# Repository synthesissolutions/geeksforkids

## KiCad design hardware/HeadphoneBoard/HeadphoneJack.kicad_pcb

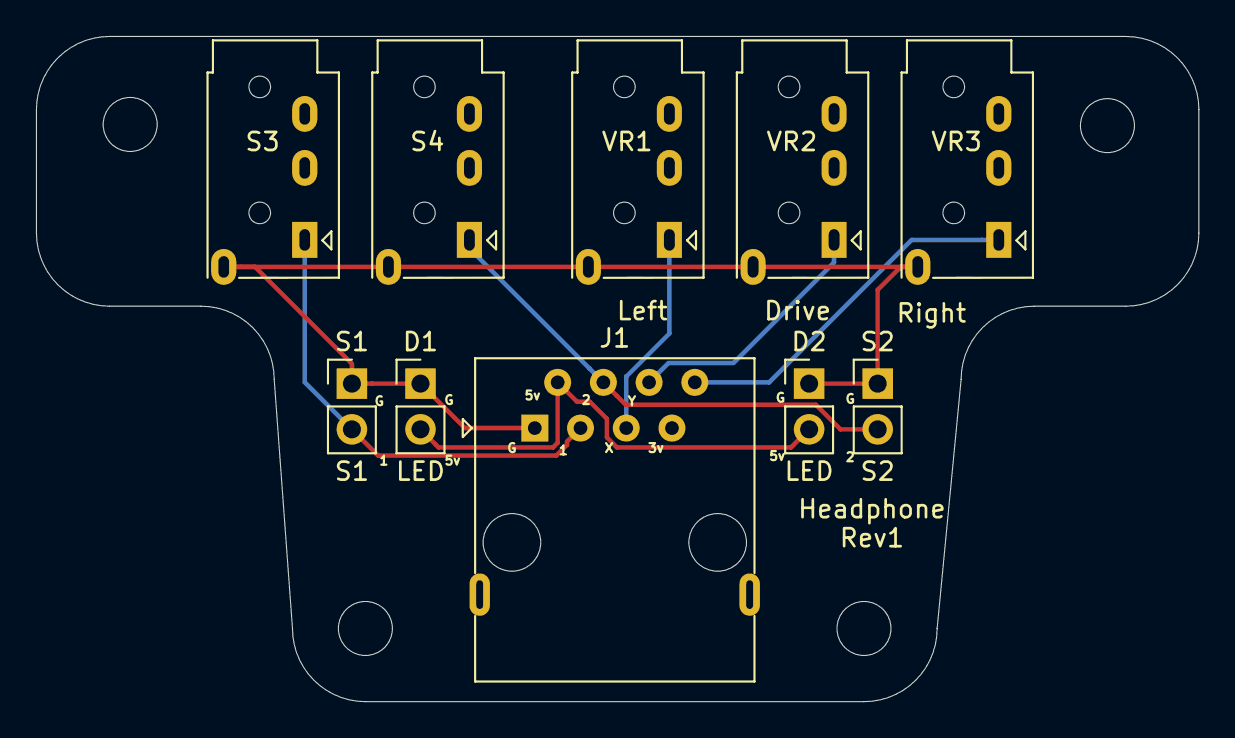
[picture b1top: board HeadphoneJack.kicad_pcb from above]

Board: 2 copper layers, 64.6 x 37.0 mm, 10 parts (0 on the bottom side), 7 nets.

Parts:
D1, D2: LED; PinHeader_1x02_P2.54mm_Vertical
J1: 8P8C; RJ45_x08_Horizontal_tabs
S1: S1; PinHeader_1x02_P2.54mm_Vertical
S2: S2; PinHeader_1x02_P2.54mm_Vertical
S3: S1; Jack_3.5mm_PJ320A_Horizontal_Short
S4: S2; Jack_3.5mm_PJ320A_Horizontal_Short
VR1: Left; Jack_3.5mm_PJ320A_Horizontal_Short
VR2: Drive; Jack_3.5mm_PJ320A_Horizontal_Short
VR3: Right; Jack_3.5mm_PJ320A_Horizontal_Short

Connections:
+5V: D1.2, D2.2, J1.2
GND: D1.1, D2.1, J1.1, S1.1, S2.1, S3.S, S4.S, VR1.S, VR2.S, VR3.S
unnamed: J1.3, S1.2, S3.T
unnamed: J1.4, S2.2, S4.T
unnamed: J1.5, VR1.T
unnamed: J1.6, VR2.T
unnamed: J1.8, VR3.T

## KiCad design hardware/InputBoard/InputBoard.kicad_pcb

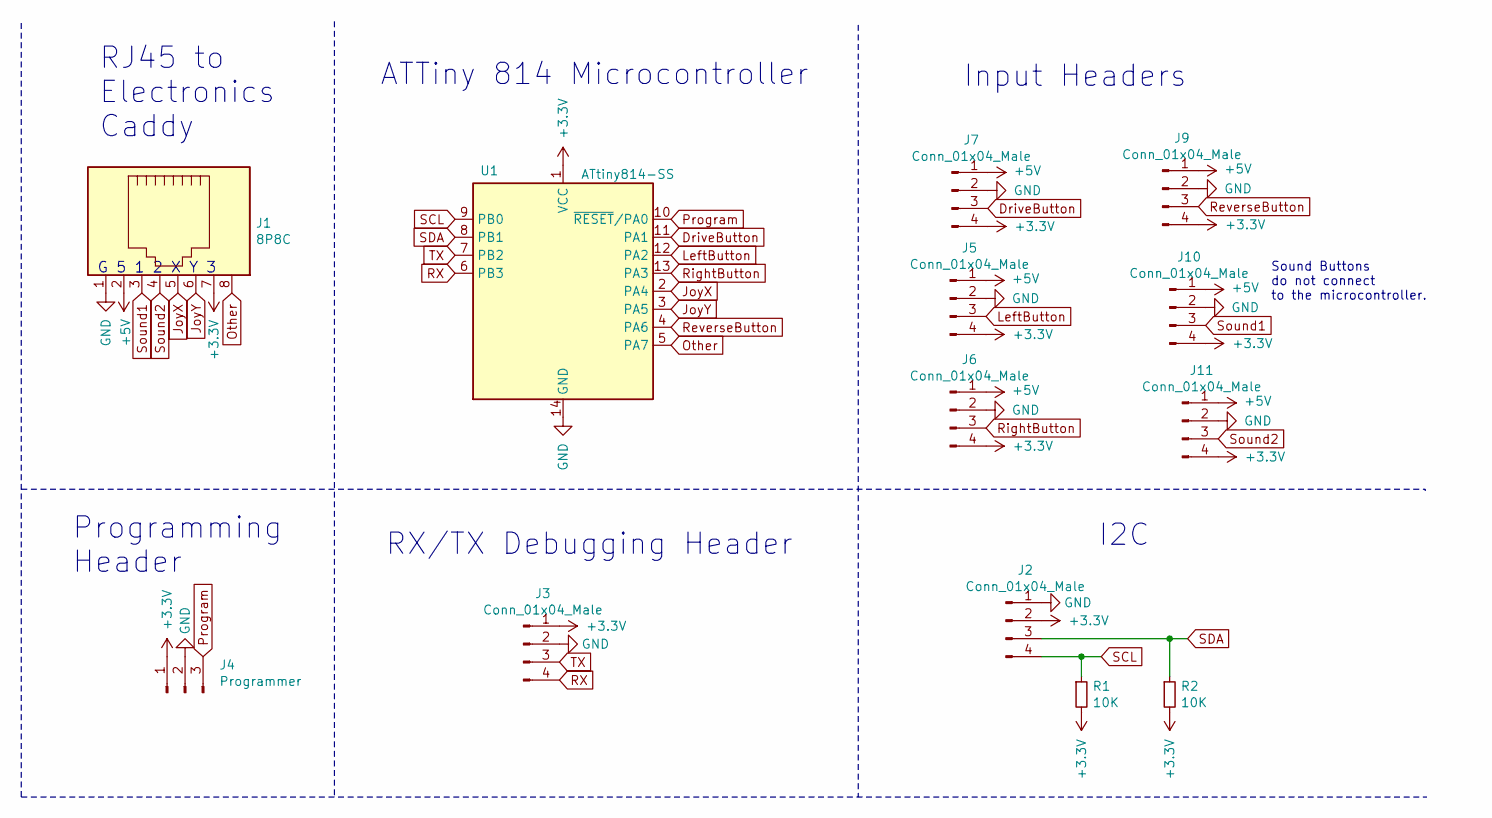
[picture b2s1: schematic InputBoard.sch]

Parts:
J1: 8P8C; RJ45_x08_Horizontal_tabs
J2: Conn_01x04_Male; JST_SH_SM04B-SRSS-TB_1x04-1MP_P1.00mm_Horizontal
J3, J5, J6, J7, J9, J10, J11: Conn_01x04_Male; PinHeader_1x04_P2.54mm_Vertical
J4: Programmer; PinHeader_1x03_P2.54mm_Vertical
R1, R2: 10K; R_0805_2012Metric_Pad1.15x1.40mm_HandSolder
U1: ATtiny814-SS; SOIC-14_3.9x8.7mm_P1.27mm

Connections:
+3V3: J1.7, J2.2, J3.1, J4.1, J5.4, J6.4, J7.4, J9.4, J10.4, J11.4, R1.2, R2.2, U1.1 (VCC)
+5V: J1.2, J5.1, J6.1, J7.1, J9.1, J10.1, J11.1
DriveButton: J7.3, U1.11 (PA1)
GND: J1.1, J2.1, J3.2, J4.2, J5.2, J6.2, J7.2, J9.2, J10.2, J11.2, U1.14 (GND)
JoyX: J1.5, U1.2 (PA4)
JoyY: J1.6, U1.3 (PA5)
LeftButton: J5.3, U1.12 (PA2)
Other: J1.8, U1.5 (PA7)
Program: J4.3, U1.10 (~RESET~/PA0)
RX: J3.4, U1.6 (PB3)
ReverseButton: J9.3, U1.4 (PA6)
RightButton: J6.3, U1.13 (PA3)
SCL: J2.4, R1.1, U1.9 (PB0)
SDA: J2.3, R2.1, U1.8 (PB1)
Sound1: J1.3, J10.3
Sound2: J1.4, J11.3
TX: J3.3, U1.7 (PB2)

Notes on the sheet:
G 5 1 2 X Y 3
Input Headers
Sound Buttons do not connect to the microcontroller.
ATTiny 814 Microcontroller
RJ45 to Electronics Caddy
Programming Header
RX/TX Debugging Header
I2C

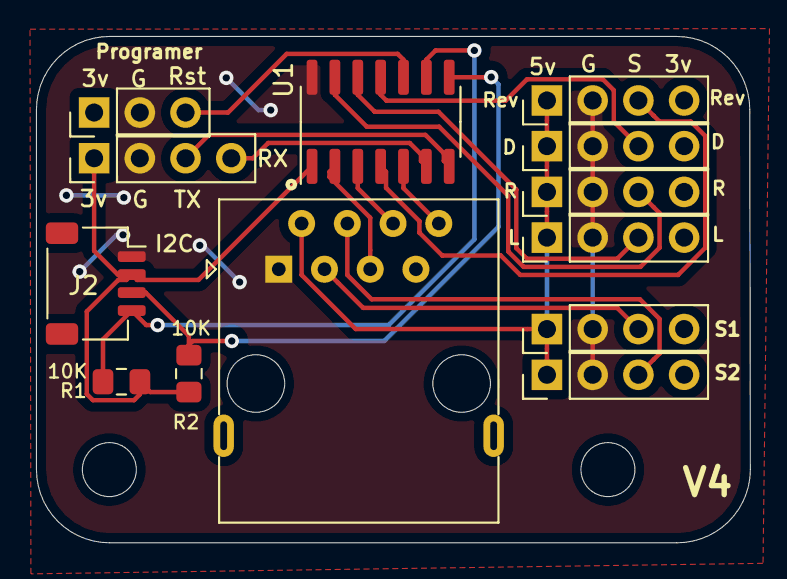
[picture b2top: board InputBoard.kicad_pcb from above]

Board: 2 copper layers, 39.7 x 28.1 mm, 13 parts (0 on the bottom side), 17 nets.

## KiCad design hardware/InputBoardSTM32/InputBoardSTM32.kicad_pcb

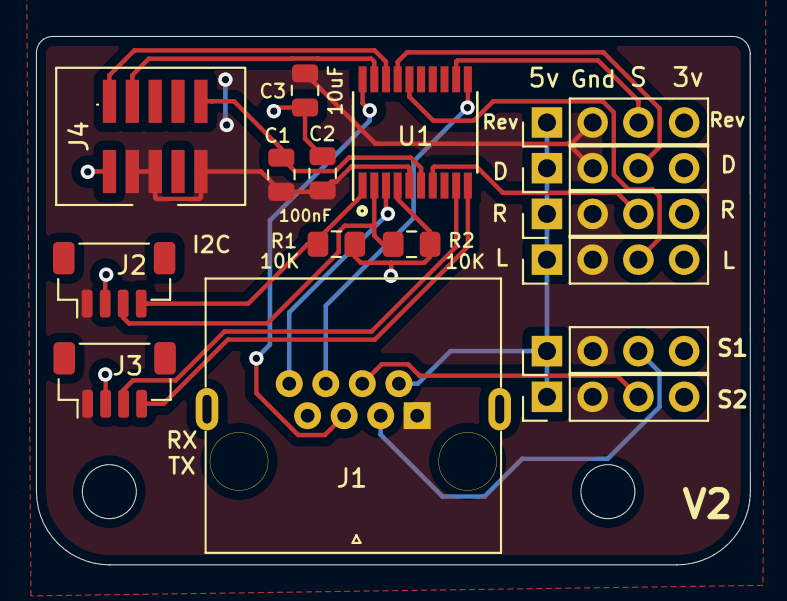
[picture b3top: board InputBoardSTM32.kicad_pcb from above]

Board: 2 copper layers, 39.7 x 29.4 mm, 16 parts (0 on the bottom side), 19 nets.

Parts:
C1, C2: 100nF; C_0805_2012Metric
C3: 10uF; C_0805_2012Metric
J1: 8P8C; RJ45_x08_Tab_Up
J2, J3: Conn_01x04_Male; JST_SH_BM04B-SRSS-TB_1x04-1MP_P1.00mm_Vertical
J4: Conn_ARM_JTAG_SWD_10; JTAG_SWD_SMD
J5, J6, J7, J9, J10, J11: Conn_01x04_Male; PinHeader_1x04_P2.54mm_Vertical
R1, R2: 10K; R_0805_2012Metric_Pad1.15x1.40mm_HandSolder
U1: STM32G031F4Px; TSSOP-20_4.4x6.5mm_P0.65mm

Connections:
+3V3: C2.1, C3.1, J1.7, J2.2, J3.2, J4.1, J5.4, J6.4, J7.4, J9.4, J10.4, J11.4, R1.2, R2.2, U1.4
+5V: J1.2, J5.1, J6.1, J7.1, J9.1, J10.1, J11.1
/RESET: C1.1, J4.10, U1.6
DriveButton: J7.3, U1.17
GND: C1.2, C2.2, C3.2, J1.1, J2.1, J3.1, J4.3, J4.5, J4.9, J5.2, J6.2, J7.2, J9.2, J10.2, J11.2, U1.5
JoyX: J1.5, U1.20
JoyY: J1.6, U1.11
LeftButton: J5.3, U1.16
Other: J1.8, U1.3
RX: J3.4, U1.10
ReverseButton: J9.3, U1.12
RightButton: J6.3, U1.7
SCL: J2.4, R1.1, U1.1
SDA: J2.3, R2.1, U1.2
SWCLK: J4.4, U1.19
SWDIO: J4.2, U1.18
Sound1: J1.3, J10.3
Sound2: J1.4, J11.3
TX: J3.3, U1.9

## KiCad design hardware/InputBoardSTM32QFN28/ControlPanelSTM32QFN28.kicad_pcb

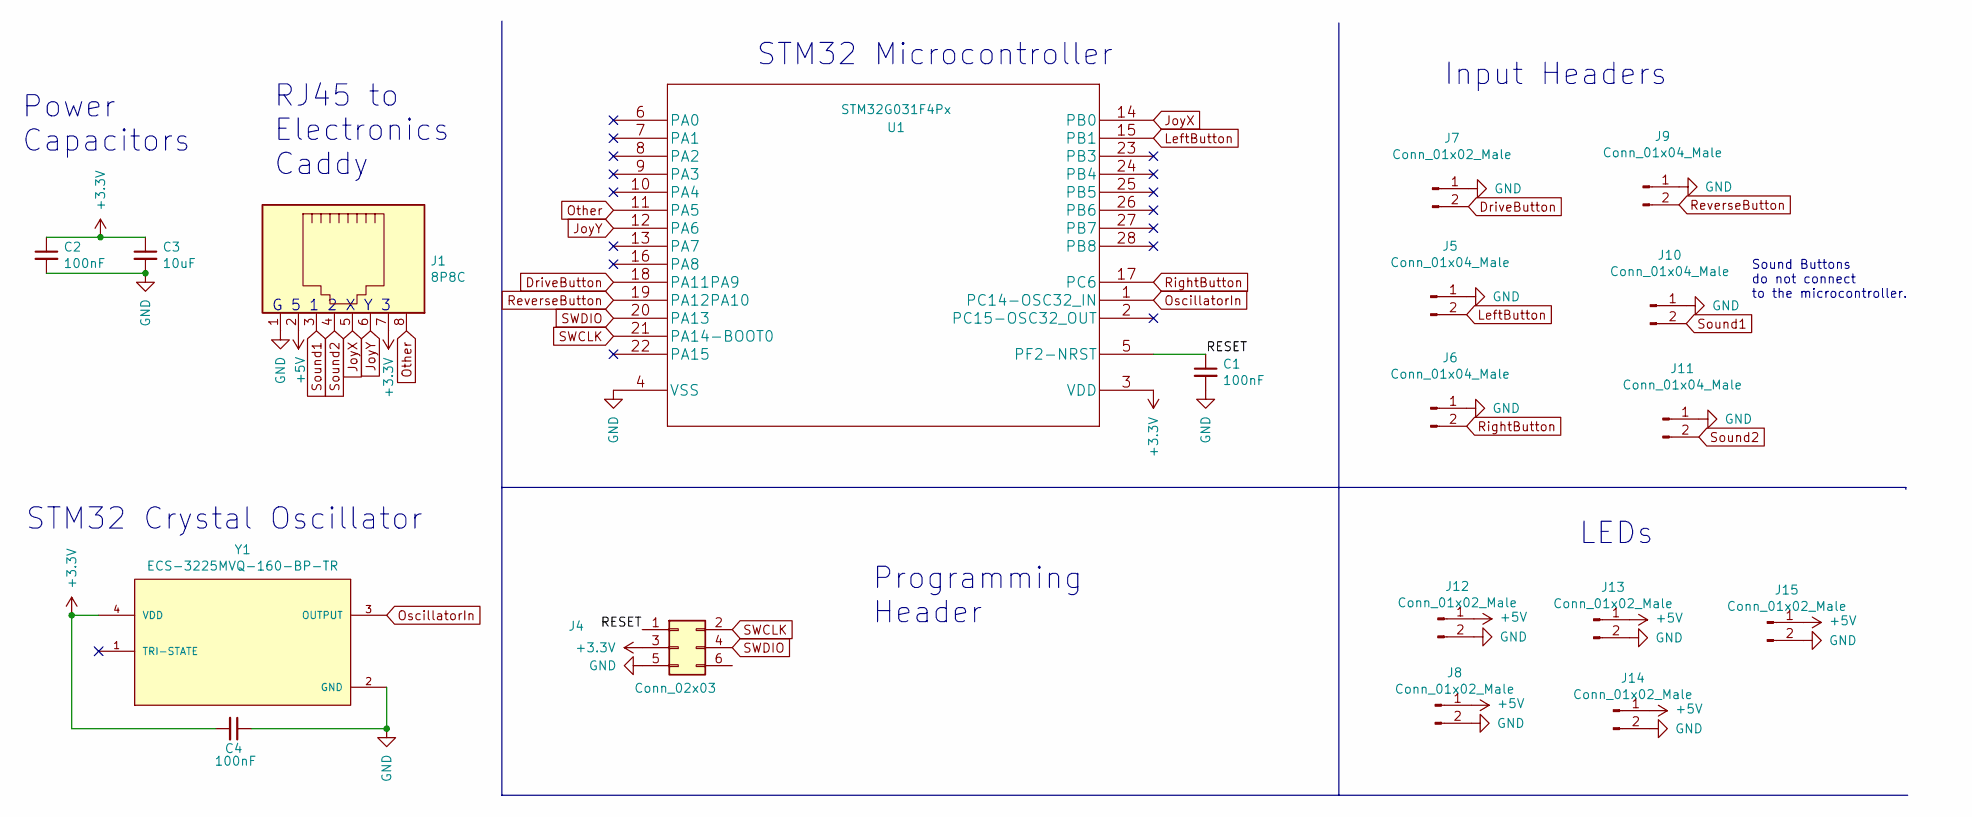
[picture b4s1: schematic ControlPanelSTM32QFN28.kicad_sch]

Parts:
C1, C2, C4: 100nF; C_0805_2012Metric
C3: 10uF; C_0805_2012Metric
J1: 8P8C; RJ45_x08_Tab_Up
J4: Conn_02x03; PinHeader_2x03_P2.54mm_Vertical
J5, J6, J9, J10, J11: Conn_01x04_Male; JST_XH_B2B-XH-A_1x02_P2.50mm_Vertical
J7, J8, J12, J13, J14, J15: Conn_01x02_Male; JST_XH_B2B-XH-A_1x02_P2.50mm_Vertical
U1: STM32G031F4Px; STM32G031G8U6
Y1: ECS-3225MVQ-160-BP-TR; OSC_ECS-3225MVQ-160-BP-TR

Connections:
+3V3: C2.1, C3.1, C4.2, J1.7, J4.3, U1.3 (VDD), Y1.4 (VDD)
+5V: J1.2, J8.1, J12.1, J13.1, J14.1, J15.1
/RESET: C1.1, J4.1, U1.5 (PF2-NRST)
DriveButton: J7.2, U1.18 (PA11PA9)
GND: C1.2, C2.2, C3.2, C4.1, J1.1, J4.5, J5.1, J6.1, J7.1, J8.2, J9.1, J10.1, J11.1, J12.2, J13.2, J14.2, J15.2, U1.4 (VSS), Y1.2 (GND)
JoyX: J1.5, U1.14 (PB0)
JoyY: J1.6, U1.12 (PA6)
LeftButton: J5.2, U1.15 (PB1)
OscillatorIn: U1.1 (PC14-OSC32_IN), Y1.3 (OUTPUT)
Other: J1.8, U1.11 (PA5)
ReverseButton: J9.2, U1.19 (PA12PA10)
RightButton: J6.2, U1.17 (PC6)
SWCLK: J4.2, U1.21 (PA14-BOOT0)
SWDIO: J4.4, U1.20 (PA13)
Sound1: J1.3, J10.2
Sound2: J1.4, J11.2

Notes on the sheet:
STM32 Microcontroller
RJ45 to Electronics Caddy
LEDs
Programming Header
Power Capacitors
Input Headers
STM32 Crystal Oscillator
G 5 1 2 X Y 3
Sound Buttons do not connect to the microcontroller.

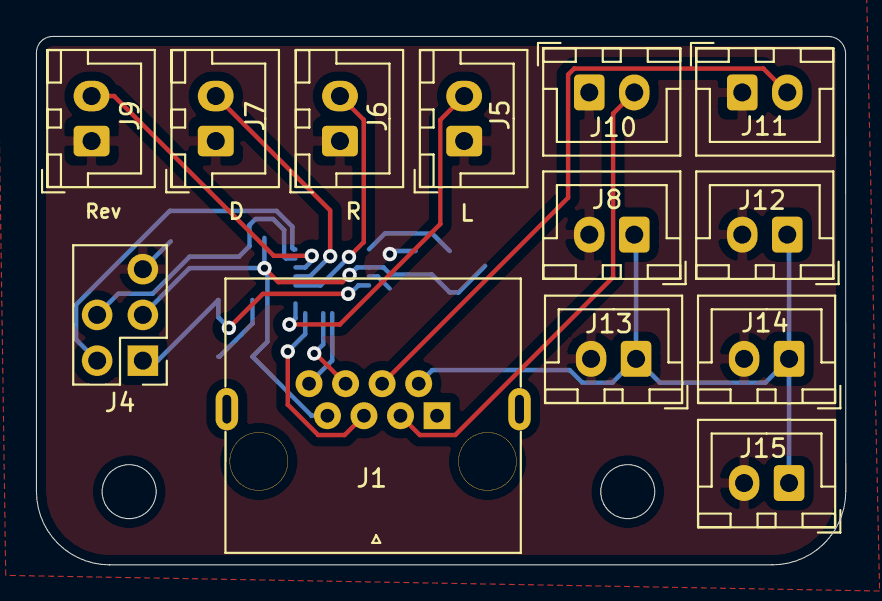
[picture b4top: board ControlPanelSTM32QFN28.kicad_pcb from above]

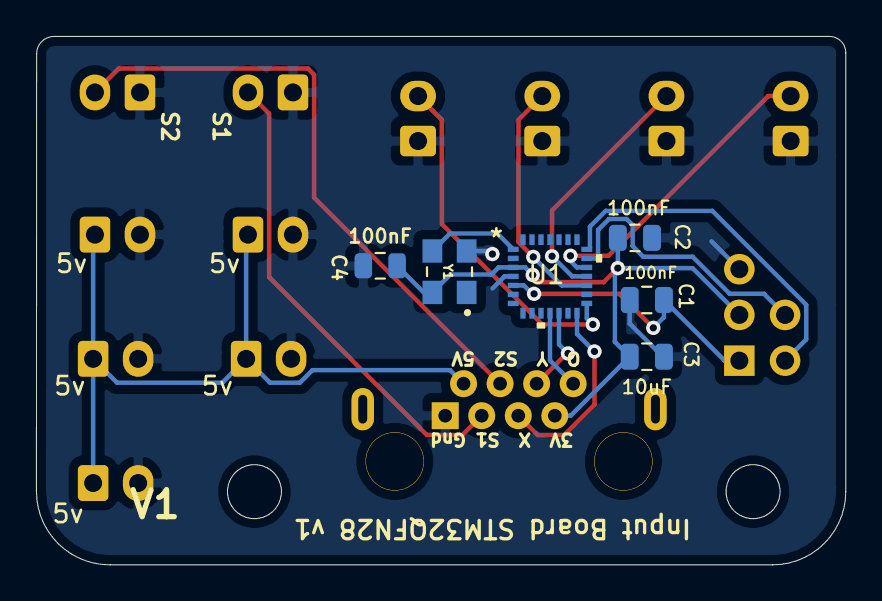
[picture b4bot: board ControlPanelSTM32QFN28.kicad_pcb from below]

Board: 2 copper layers, 45.0 x 29.4 mm, 19 parts (6 on the bottom side), 16 nets.

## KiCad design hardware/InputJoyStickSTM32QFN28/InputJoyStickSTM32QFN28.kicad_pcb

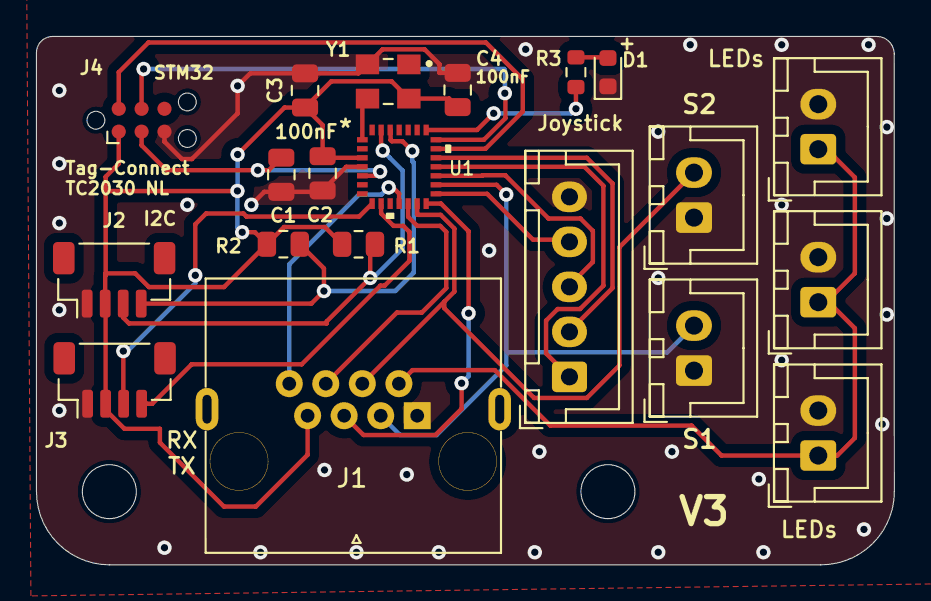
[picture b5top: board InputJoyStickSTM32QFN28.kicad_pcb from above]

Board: 2 copper layers, 47.7 x 29.4 mm, 20 parts (0 on the bottom side), 22 nets.

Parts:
C1, C2, C4: 100nF; C_0805_2012Metric
C3: 10uF; C_0805_2012Metric
D1: LED_Small; LED_0603_1608Metric
J1: 8P8C; RJ45_x08_Tab_Up
J2, J3: Conn_01x04_Male; JST_SH_BM04B-SRSS-TB_1x04-1MP_P1.00mm_Vertical
J4: TagConnect_TC2030-NL; Tag-Connect_TC2030-IDC-NL_2x03_P1.27mm_Vertical
J5: Conn_01x05_Male; JST_XH_B5B-XH-A_1x05_P2.50mm_Vertical
J6, J7, J8, J9, J10: Conn_01x02_Male; JST_XH_B2B-XH-A_1x02_P2.50mm_Vertical
R1, R2: 10K; R_0805_2012Metric
R3: 470; R_0603_1608Metric
U1: STM32G031F4Px; STM32G031G8U6
Y1: ECS-3225MVQ-160-BP-TR; OSC_ECS-3225MVQ-160-BP-TR

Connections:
+3V3: C2.1, C3.1, C4.2, J1.7, J2.2, J3.2, J4.1 (VCC), R1.2, R2.2, U1.3 (VDD), Y1.4 (VDD)
+5V: J1.2, J7.1, J9.1, J10.1
/RESET: C1.1, J4.3 (~RESET), U1.5 (PF2-NRST)
DriveButton: J5.1, U1.18 (PA11PA9)
GND: C1.2, C2.2, C3.2, C4.1, D1.1 (K), J1.1, J2.1, J3.1, J4.5 (GND), J5.5, J6.1, J7.2, J8.1, J9.2, J10.2, U1.4 (VSS), Y1.2 (GND)
JoyX: J1.5, U1.14 (PB0)
JoyY: J1.6, U1.12 (PA6)
LeftButton: J5.4, U1.15 (PB1)
unnamed: D1.2 (A), R3.1
OscillatorIn: U1.1 (PC14-OSC32_IN), Y1.3 (OUTPUT)
Other: J1.8, U1.11 (PA5)
RX: J3.4, U1.9 (PA3)
ReverseButton: J5.2, U1.19 (PA12PA10)
RightButton: J5.3, U1.17 (PC6)
SCL: J2.4, R1.1, U1.26 (PB6)
SDA: J2.3, R2.1, U1.27 (PB7)
SWCLK: J4.4 (SWCLK), U1.21 (PA14-BOOT0)
SWDIO: J4.2 (SWDIO), U1.20 (PA13)
Sound1: J1.3, J6.2, U1.16 (PA8)
Sound2: J1.4, J8.2, U1.13 (PA7)
TX: J3.3, U1.8 (PA2)
USER_LED: R3.2, U1.22 (PA15)

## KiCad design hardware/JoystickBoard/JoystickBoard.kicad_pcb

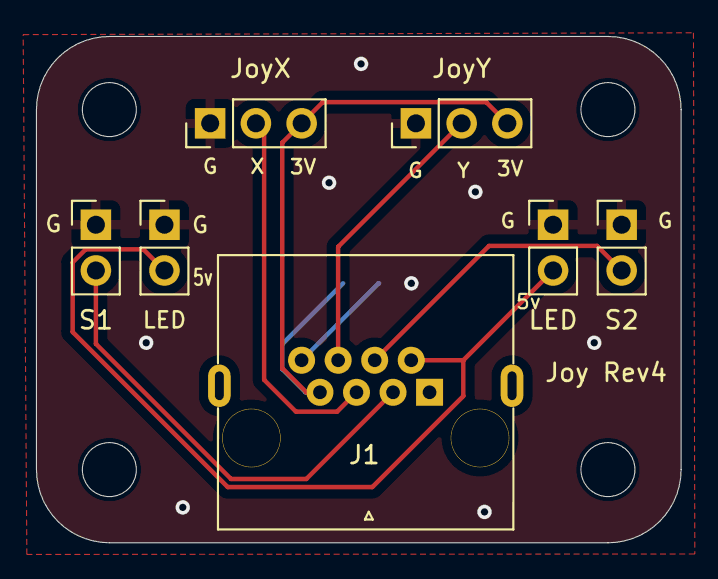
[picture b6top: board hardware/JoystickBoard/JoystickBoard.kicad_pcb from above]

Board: 2 copper layers, 35.8 x 28.1 mm, 12 parts (1 on the bottom side), 8 nets.

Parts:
H1, H2, H3, H4: MountingHole_3mm
J1: 8P8C; RJ45_x08_Tab_Up
J2: S1; PinHeader_1x02_P2.54mm_Vertical
J3: S2; PinHeader_1x02_P2.54mm_Vertical
J4: JoyX; PinHeader_1x03_P2.54mm_Vertical
J5: JoyY; PinHeader_1x03_P2.54mm_Vertical
J6, J7: LED; PinHeader_1x02_P2.54mm_Vertical
R1: 10K; R_0805_2012Metric_Pad1.20x1.40mm_HandSolder

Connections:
+3.3V: J1.7, J4.3, J5.3, R1.2
+5V: J1.2, J6.2, J7.2
GND: J1.1, J2.1, J3.1, J4.1, J5.1, J6.1, J7.1
JoystickX: J1.5, J4.2
JoystickY: J1.6, J5.2
unnamed: J1.8, R1.1
Sound1: J1.3, J2.2
Sound2: J1.4, J3.2

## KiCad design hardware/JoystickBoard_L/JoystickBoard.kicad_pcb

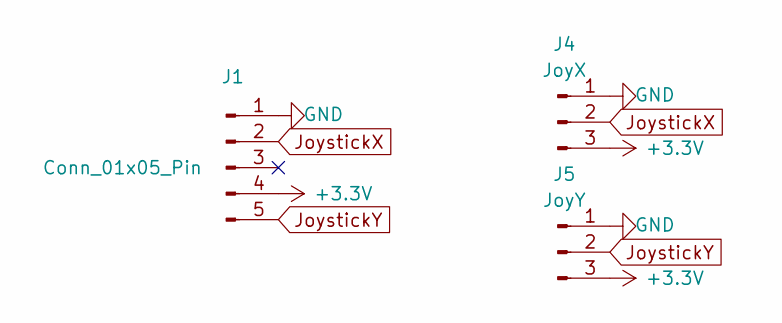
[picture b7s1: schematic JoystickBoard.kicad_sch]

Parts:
J1: Conn_01x05_Pin; JST_XH_B5B-XH-A_1x05_P2.50mm_Vertical
J4: JoyX; Analog_joystick_pot
J5: JoyY; Analog_joystick_pot

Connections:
+3.3V: J1.4, J4.3, J5.3
GND: J1.1, J4.1, J5.1
JoystickX: J1.2, J4.2
JoystickY: J1.5, J5.2

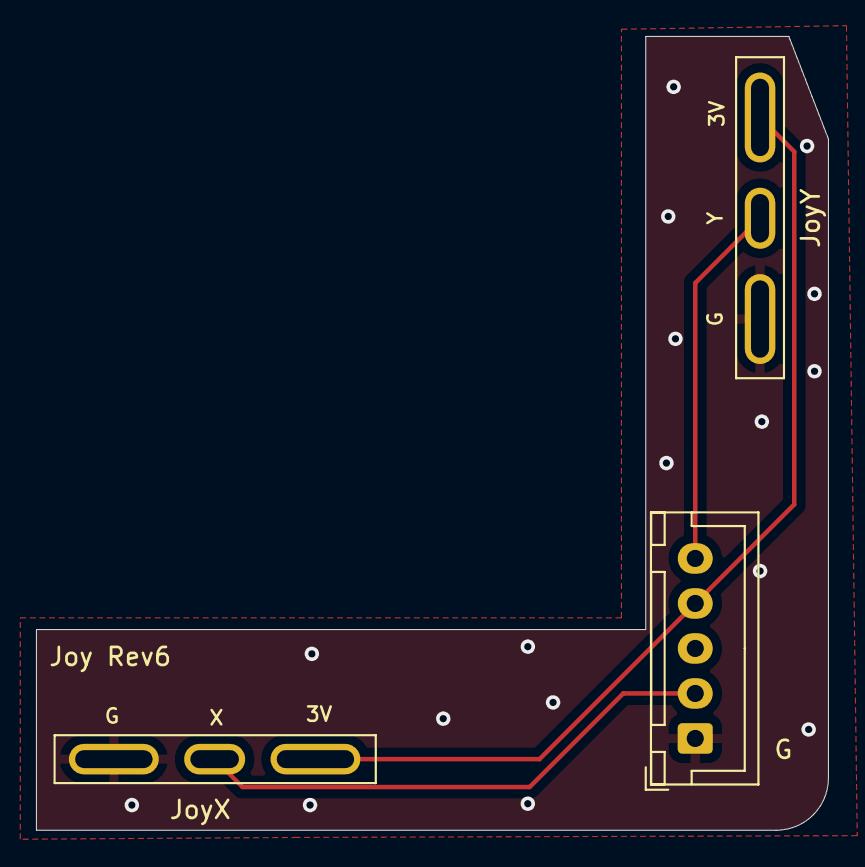
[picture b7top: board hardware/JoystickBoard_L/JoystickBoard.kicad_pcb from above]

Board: 2 copper layers, 44.0 x 44.1 mm, 3 parts (0 on the bottom side), 4 nets.

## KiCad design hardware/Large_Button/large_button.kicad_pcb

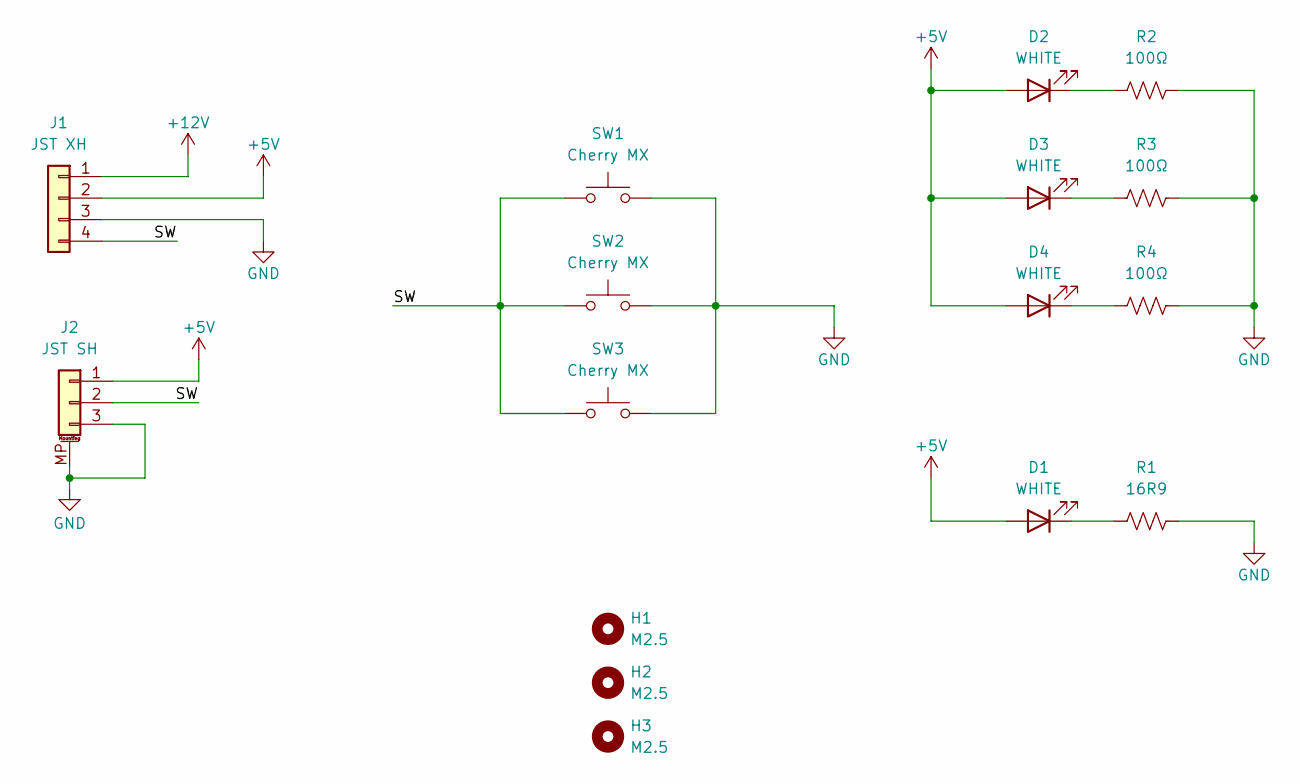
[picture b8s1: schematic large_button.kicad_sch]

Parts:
D1: WHITE; LED_PLCC_2835_Handsoldering; MPN C210322
D2, D3, D4: WHITE; LED_D3.0mm; MPN C210322
H1, H2, H3: M2.5; MountingHole_2.7mm_M2.5_DIN965
J1: JST XH; JST_XH_S4B-XH-A_1x04_P2.50mm_Horizontal; MPN C157925
J2: JST SH; JST_SH_SM03B-SRSS-TB_1x03-1MP_P1.00mm_Horizontal; MPN C160403
R1: 16R9; R_1210_3225Metric_Pad1.30x2.65mm_HandSolder; MPN C230050
R2, R3, R4: 100Ω; R_0603_1608Metric; MPN C22775
SW1, SW2, SW3: Cherry MX; SW_Cherry_MX_1.00u_PCB; MPN C400229

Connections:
+5V: D1.2 (A), D2.2 (A), D3.2 (A), D4.2 (A), J1.2, J2.1
+12V: J1.1
/SW: J1.4, J2.2, SW1.1, SW2.1, SW3.1
GND: J1.3, J2.3, J2.MP (MountPin), R1.2, R2.2, R3.2, R4.2, SW1.2, SW2.2, SW3.2
unnamed: D1.1 (K), R1.1
unnamed: D2.1 (K), R2.1
unnamed: D3.1 (K), R3.1
unnamed: D4.1 (K), R4.1

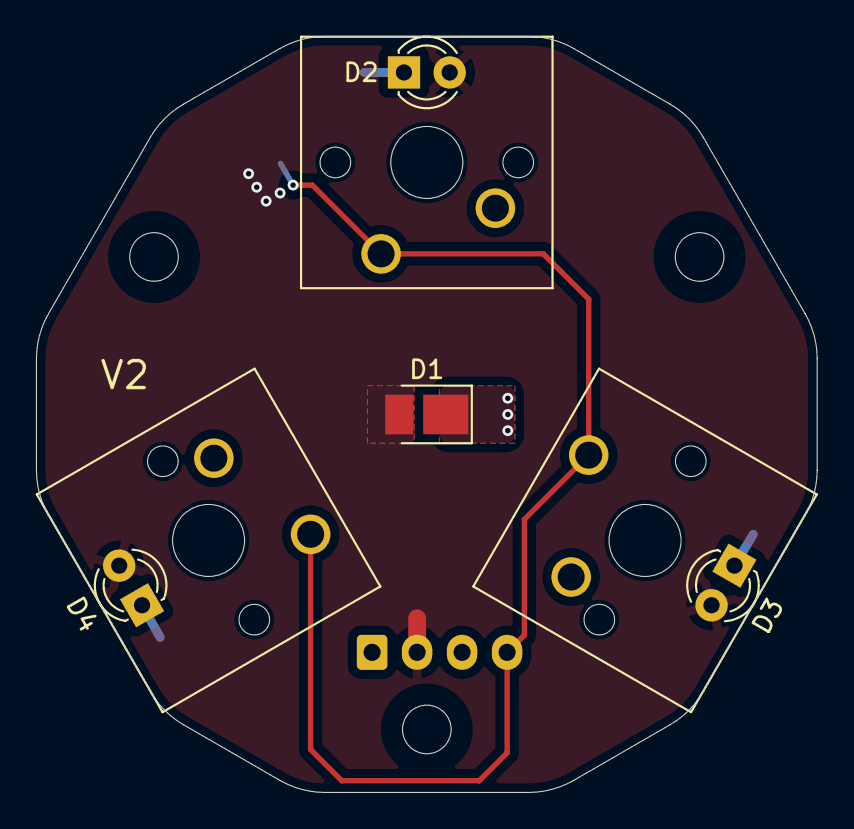
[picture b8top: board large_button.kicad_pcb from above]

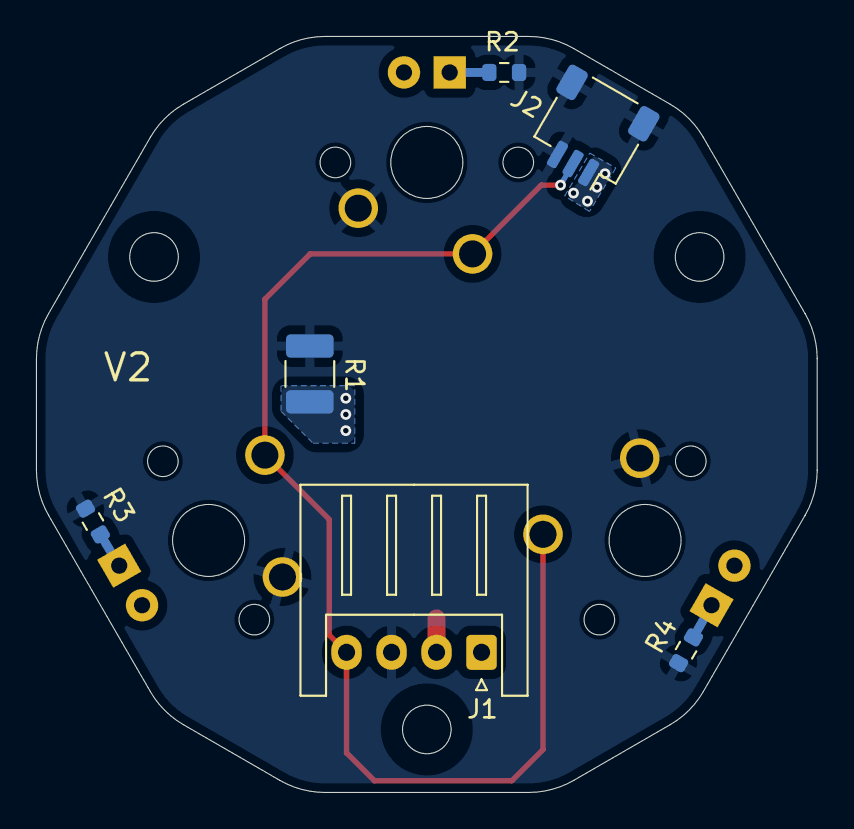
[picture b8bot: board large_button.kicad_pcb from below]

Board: 2 copper layers, 43.4 x 42.0 mm, 16 parts (6 on the bottom side), 7 nets.

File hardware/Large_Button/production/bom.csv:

Designator,Footprint,Quantity,Value,LCSC Part #
D1,LED_PLCC_2835_Handsoldering,1,WHITE,C210322
J1,JST_XH_S4B-XH-A_1x04_P2.50mm_Horizontal,1,JST XH,C157925
J2,JST_SH_SM03B-SRSS-TB_1x03-1MP_P1.00mm_Horizontal,1,JST SH,C160403
R1,1210,1,36R0,C5121553
"R2, R3, R4",0603,3,100Ω,C22775

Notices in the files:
parts and their libraries:
Copyright 2021 Accelerated Designs. All rights reserved.
